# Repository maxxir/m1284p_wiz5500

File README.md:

# m1284p_wiz5500

*Read this in other languages: [English](README.md), [Русский](README.ru.md).*

Lots of projects using ATMEGA 1284p(644p partially) and Ethernet NIC Wiznet 5500.

Based on W5500 EVB examples, but heavily modified.

Building in Eclipse Kepler with AVR-Eclipse plugin and avr-gcc 4.9.2 toolchain.

## Hardware part of the projects

* [Kicad open hardware](../master/KiCad_M644_breakout_v1.2d/) 

#### This is my own m644p/m1284p custom board looks like:

#### Tested system photo:

## Software part. What done ( In order of increasing complexity and date of creation )

1. [Wiznet Loopback TCP/UDP Static IP](../master/03_m1284p_WIZNET_loopback_STATIC_IP/)
2. [Wiznet Loopback TCP/UDP DHCP IP](../master/04_m1284p_WIZNET_loopback_DHCP/)
3. [DNS example](../master/05_m1284p_WIZNET_DNS_client/)
4. [SNTP + DNS example](../master/06_m1284p_WIZNET_DNS_SNTP_client/)
5. [Telnet server example](../master/07_m1284p_WIZNET_telnets_basic/)
6. [ICMP aka ping example](../master/08_m1284p_WIZNET_ICMP_aka_ping/)
7. [Simple Web Server (one page with HTTP POST/GET queries)](../master/09_m1284p_WIZNET_simple_webserver/)
8. [HTTPD Web Server with all contents in AVR FLASH (with AJAX queries)](../master/11_m1284p_WIZNET_HTTPServer_FLASH_pages/)
9. [HTTPD Web Server with all content on SD card (Chang FAT FS lib using) (with AJAX queries)](../master/12_m1284p_WIZNET_HTTPServer_SDCARD_pages/)
10. [FTPC example (only active mode sorry) with store content on SD card (console dialog from serial terminal like putty..)](../master/14_m1284p_WIZNET_FTPC_FATFS/)
11. [FTPD example (both active-passive modes working) with store content on SD card, checked on FTP clients: Windows 7 cmd, FAR, Total commander, WinSCP.](../master/15_m1284p_WIZNET_FTPD_FATFS/)
12. [Combined HTTPD + FTPD for  dynamic upload WEB server pages, with all content on SD card (Chang FAT FS lib using) (with AJAX queries)](../master/16_m1284p_WIZNET_HTTPD_FTPD_FATFS_SDCARD/)
13. ZEVERO SD PetitFS Bootloader for both [M1284p](../master/bootloader_zevero_sd_m1284p_make/)/[M644p](../master/bootloader_zevero_sd_m644p_make/)
14. Bootloaded code: Combined Wiznet Loopback TCP/UDP Static IP + FTPD server (for bootloading via FTP client) + SD-bootloader ZEVERO, working on [M644p](../master/18_m644p_BTLD_WIZNET_LOOPBACK_FTPD_FATFS_SDCARD/)/[M1284p](../master/18_m1284p_BTLD_WIZNET_LOOPBACK_FTPD_FATFS_SDCARD/)
15. [Bootloaded code: Combined HTTPD server (with AJAX) + FTPD server (for bootloading via FTP client and upload WEB server contents) + SD-bootloader ZEVERO, working on M1284p only](../master/17_m1284p_BTLD_WIZNET_HTTPD_FTPD_FATFS_SDCARD/)
16. [IOT Blynk client Example with Blynk smartphone application (checked only Android side) - NO Arduino CODE, used Wiznet Sockets](../master/19_m1284p_WIZNET_blynk/)
17. [Bootloaded code: IOT BLYNK client combined with FTPD server (for bootloading via FTP client)+ SD-bootloader ZEVERO, working on M1284p only](../master/20_m1284p_BTLD_WIZNET_BLYNK_FTPD_FATFS_SDCARD/)
18. [TFTP client](../master/21_m1284p_WIZNET_TFTP_client_FATFS/)
19. [MQTT client](../master/22_m1284p_WIZNET_MQTT/)

#### Blynk application screenshot:

[//]: # (TODO:  Add all other links here)

## What TODO:

All done.

## Remarks:
* [m1284P schematic](../master/KiCad_M644_breakout_v1.2d/Pictures/M644_breakout_v1.2d_schematic.png/)
* [m1284P typical connection diagram](../master/KiCad_M644_breakout_v1.2d/Pictures/M644_connection_schematic.png/)
* [m1284P Board pinmap](../master/KiCad_M644_breakout_v1.2d/Pictures/M644_breakout_v1.2d_pinmap.png/)
* [Blynk IOT Application QR-code](../master/19_m1284p_WIZNET_blynk/Blynk_application/app2_m1284p_and_W5500_QR.png/)

[>>Hardware and Software parts (no Blynk) discussion your are welcome here..](https://www.avrfreaks.net/forum/need-w5500-example-c-tcp)

[>>Blynk part discussion your are welcome here..](https://community.blynk.cc/t/port-from-w5500-evb-to-atmega1284p-w5500-wiznet-sockets-library-without-arduino/35235)

## Author porting to AVR m1284p/m644p
* **Ibragimov Maksim aka maxxir**

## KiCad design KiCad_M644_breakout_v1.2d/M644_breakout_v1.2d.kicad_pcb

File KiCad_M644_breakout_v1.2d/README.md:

# AtMega 8535/16/32/324/644/1284 generic board

### Briefly about the features of the scheme:
* Nearly all GPIO pins connected to PLS terminals.
* Two GPIOs are connected: button (SW1 / PC5) and the LED (LED1 / PC4).
* External pull-up on UART RX0 / RX1.
* R-dividers for 3.3V-TTL on UART TX0 / TX1.
* SPI pins for 3 devices connected to (for example):
Ethernet (Wiz5500 / ENC28J60), Sd-Card, CAN MCP2515 and so on ...
* Compatible with **Arduino Sanguino/Mightycore**

#### Schematic:

#### This is my own custom board looks like:

#### Pinmap board (Sanguino notation):

## Author
* **Ibragimov Maksim aka maxxir**
08/04/2019

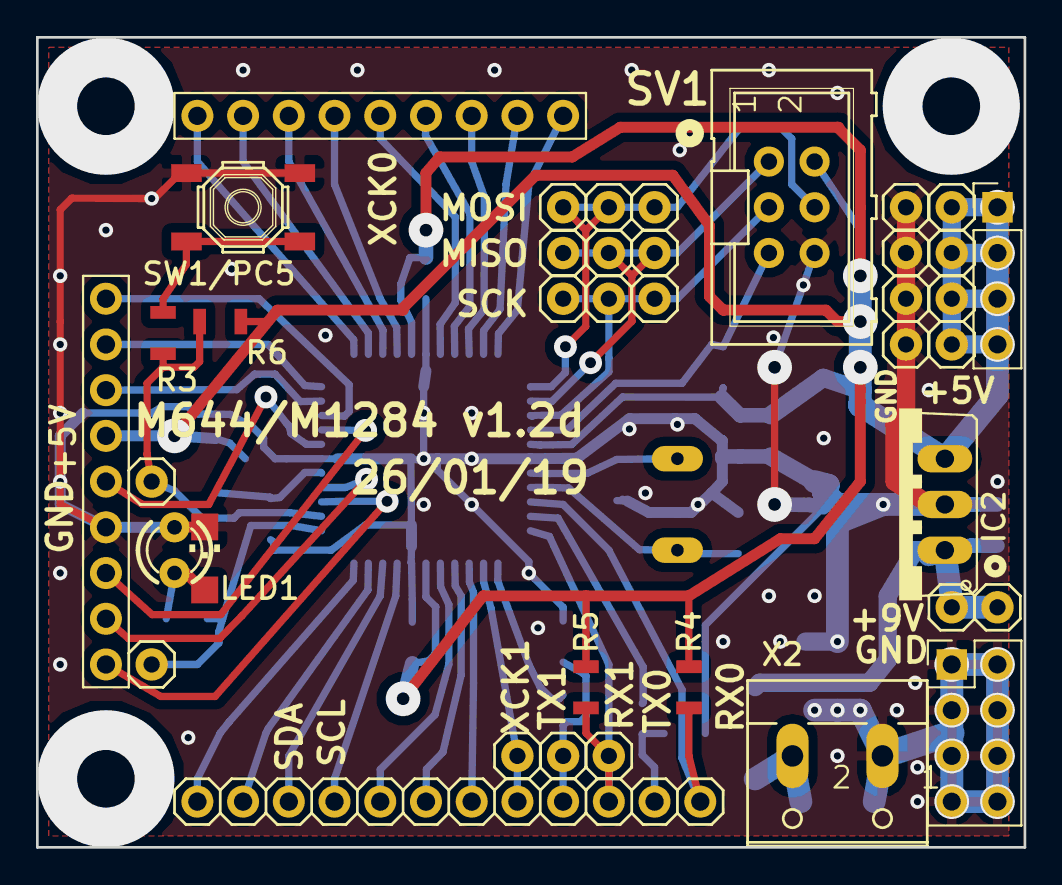
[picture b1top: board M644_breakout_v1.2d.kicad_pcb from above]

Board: 2 copper layers, 54.9 x 45.0 mm, 60 parts (0 on the bottom side), 45 nets.

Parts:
C1, C2: 18pf; C0805H
C3, C5, C7, C8, C9, C10, C11: 0.1mF; C0805H
C4: 10uF; C0805H
C6: 22uF; C0805H
C12: 100uF; D_7343-31R
D1: SM4007; DO214AA
D3: SM6T15CA; SMBJ
IC1: ATMEGA16/32/644/1284; TQFP44
IC2: 78TV; TO220V
JP1, JP2: PIN1x9; 1X09-BIG
JP3: PIN1x12; 1X12
JP4, JP5, JP6, JP7, JP8, JP9, JP10, JP11, JP12, JP13, JP14, JP15, JP16, JP17, JP19, JP20, JP21, JP22, JP24, JP25, JP26, JP27, JP28, JP29: PINx1; 1X01
L2: 10uH; L3216C
LED1: LED_RED/PC4/20; LED3MM
LED1_SMD1: LED_RED/PC4/20; CHIPLED_1206
Q1: 16Mhz; QS
R1: 1Kom; R0805H
R2: 4.7KOm; R0805H
R3: 510Om; R0805H
R4, R5: 10KOm; R0805H
R6: 10kOm; R0805H
R7, R8: 1Kom; R0805
R9, R10: 2Kom; R0805H
SV1: ISP_6PIN; ML6
SW1/PC5: SMD_TACT_4x4; SW_TACT_SMALL
X2: DG300-5.0-02P-12; W237-102

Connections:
/AREF: C3.P$2, IC1.29, JP2.5
/MISO: IC1.2, JP6.1, JP7.1, JP12.1, SV1.1
/MOSI: IC1.1, JP8.1, JP9.1, JP13.1, SV1.4
/PA0: IC1.37, JP1.6
/PA1: IC1.36, JP1.7
/PA2: IC1.35, JP1.8
/PA3: IC1.34, JP1.9
/PA4: IC1.33, JP2.2
/PA5: IC1.32, JP2.3
/PA6: IC1.31, JP2.1
/PA7: IC1.30, JP2.7
/PB0: IC1.40, JP1.5
/PB1: IC1.41, JP1.4
/PB2: IC1.42, JP1.3
/PB3: IC1.43, JP1.2
/PB4: IC1.44, JP1.1
/PC0: IC1.19, JP3.9
/PC1: IC1.20, JP3.10
/PC2: IC1.21, JP3.11
/PC3: IC1.22, JP3.12
/PC4: IC1.23, JP28.1, R1.P$1
/PC5: IC1.24, JP27.1, R3.P$2, R6.P$2
/PC6: IC1.25, JP2.9
/PC7: IC1.26, JP2.8
/PD0: IC1.9, JP3.1, R4.P$1
/PD1: IC1.10, R8.1
/PD1': JP3.2, R8.2, R10.P$1
/PD2: IC1.11, JP3.3, JP24.1, R5.P$1
/PD3: IC1.12, R7.1
/PD3': JP3.4, JP25.1, R7.2, R9.P$1
/PD4: IC1.13, JP3.5, JP26.1
/PD5: IC1.14, JP3.6
/PD6: IC1.15, JP3.7
/PD7: IC1.16, JP3.8
/RESET: IC1.4, R2.P$1, SV1.5
/SCK: IC1.3, JP4.1, JP5.1, JP11.1, SV1.3
GND: C1.P$2, C2.P$2, C3.P$1, C4.P$2, C5.P$2, C6.P$2, C7.P$2, C8.P$1, C9.P$1, C10.P$1, C11.P$2, C12.-, D3.A, IC1.6, IC1.18, IC1.28, IC1.39, IC2.2, JP2.6, JP19.1, JP20.1, JP21.1, JP22.1, LED1.K, LED1_SMD1.C, R9.P$2, R10.P$2, SV1.6, SW1/PC5.3, SW1/PC5.4, X2.1
unnamed: C1.P$1, IC1.7, Q1.2
unnamed: C2.P$1, IC1.8, Q1.1
unnamed: C4.P$1, C5.P$1, D1.C, IC2.1, JP10.1, JP29.1
unnamed: C11.P$1, IC1.27, L2.2
unnamed: D1.A, D3.C, X2.2
unnamed: LED1.A, LED1_SMD1.A, R1.P$2
unnamed: R3.P$1, SW1/PC5.1, SW1/PC5.2
VCC: C6.P$1, C7.P$1, C8.P$2, C9.P$2, C10.P$2, C12.+, IC1.5, IC1.17, IC1.38, IC2.3, JP2.4, JP14.1, JP15.1, JP16.1, JP17.1, L2.1, R2.P$2, R4.P$2, R5.P$2, R6.P$1, SV1.2

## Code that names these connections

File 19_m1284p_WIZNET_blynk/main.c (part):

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 * OK (v1.8) Need compare local blynk.c code with modern <blynk> library - (Too old version here - 0.2.1 (On git blynk March 2019 - 0.6.x) )
 * OK (v1.8) Made fix correction blynk.h/blynk.c 16.02.2019 to match BLYNK protocol 0.6.0
 * OK (v1.9) Two feedback examples from:
 * 			 D20/PC4(digitalWrite(20))->V20(virtualRead(20))
 * 			 PWM D15/PD7(analogWrite(15))->V15(virtualRead(15))
 * 			 using push events && on change state flags
 * PS.
 * Further correction, or advices about the code from BLYNK authors (Vladimir Shimansky, Dmitriy Dumanskiy ..) is highly desirable.
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
//*********************************Timer2 PWM: BEGIN
/*
 * Handle PWM out PD7-PIN15:
 * OCR2A = 0/127/255; Duty 0/50/100%

 * Handle PWM out PD6-PIN14:
 * OCR2B = 0/127/255; Duty 0/50/100%

 */
void pwm8bit_timer2_init(void)
{
	//PWM on TIMER2 (PD7/OC2A) &&  TIMER2 (PD6/OC2B)
	// PHASE CORRECT PWM 8-bit mode setup
	// 31.25kHz FREQ OUT / 0.98kHz FREQ OUT

	// Set PD7 to OUT
	DDRD |= (1<<7);
	// Set PD6 to OUT
	DDRD |= (1<<6);
	/*
	 * Clear OCnA/OCnB/OCnC on compare
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			if(v15_changed)
			{
				v15_changed = 0; //Drop flag
				//Push message with changed V15 value (LED PWM PIN15/PD7 )
				blynk_push_virtual_pin(15);

			}
			else if(v20_changed)
			{
				v20_changed = 0; //Drop flag
				//Push message with changed V20 value (LED1 D20/PC4)
				blynk_push_virtual_pin(20);
			}
			//Every 10sec event for LED2 PIN13, and uptime device
			if(++timer_led2_push_10sec == 10)
			{
				timer_led2_push_10sec = 0; //Clear timer_led2..
				//Every 10sec toggle, and push LED2 PIN13/PD5 state to BLYNK server (widget Value Display)
				led2_tgl();
				blynk_push_pin(13);

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
	sw1_conf();//SW1 internal pull-up

	pwm8bit_timer2_init(); // PD7/OC2A used as PHASE CORRECT 8bit PWM (0.98kHz FREQ OUT)

	sei(); //re-enable global interrupts

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
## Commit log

2019-01-18 First commit for 00_m1284p_blink project
2019-01-18 First commit for 00_m1284p_blink_make
2019-01-18 Fixed text encode to UTF8, added .gitignore
2019-01-18 Delete de.innot.avreclipse.core.prefs
    Clean prj
2019-01-18 Update README.md
    Update readme
2019-01-18 Added 01_m1284p_bb00_minimum project
2019-01-18 Create global .gitignore rule
2019-01-18 Gitignore correction
2019-01-18 Add 02_m1284p_FATFS_Chang_tst project
2019-01-18 Add 02_m1284p_FATFS_LFN_Chang_tst project
2019-01-18 Add 03_m1284p_WIZNET_loopback_STATIC_IP project
2019-01-18 Add 03_m1284p_WIZNET_loopback_FATFS_template project
2019-01-18 Minor changes at <b>03_m1284p_WIZNET_loopback_FATFS_template</b>
2019-01-18 Add [04_m1284p_WIZNET_loopback_DHCP] prj
2019-01-18 Add [05_m1284p_WIZNET_DNS_client] prj
2019-01-18 Add [06_m1284p_WIZNET_DNS_SNTP_client] prj
2019-01-18 Add [07_m1284p_WIZNET_telnets_basic] prj
2019-01-18 Add [08_m1284p_WIZNET_ICMP_aka_ping] prj
2019-01-18 Add [09_m1284p_WIZNET_simple_webserver] prj
2019-01-18 Add [10_m1284p_WIZNET_HTTPServer_RAM_pages] prj
2019-01-18 Add [11_m1284p_WIZNET_HTTPServer_FLASH_pages] prj
2019-01-18 Add [11_m644p_WIZNET_HTTPServer_FLASH_pages] prj
2019-01-18 Add [12_m1284p_WIZNET_HTTPServer_SDCARD_pages] prj
2019-01-18 Minor changes [12_m1284p_WIZNET_HTTPServer_SDCARD_pages]
2019-01-18 Change text encode to UTF-8
2019-01-18 Change text encode to UTF8
2019-01-18 Add [14_m1284p_WIZNET_FTPC_FATFS_v1.2] prj
2019-01-18 Add [15_m1284p_WIZNET_FTPD_FATFS] project
2019-01-18 Add [16_m1284p_WIZNET_HTTPD_FTPD_FATFS_SDCARD] prj
2019-01-18 Add [17_m1284p_BTLD_WIZNET_HTTPD_FTPD_FATFS_SDCARD] prj
2019-01-18 Add [bootloader_zevero_sd_m1284p_make] bootloader prj
2019-01-18 Add Makefile to local .gitignore
2019-01-18 Add to [00_m1284p_blink_make] .gitignore
2019-01-18 Add double-IP config for [03_m1284p_WIZNET_loopback_FATFS_template]
2019-01-18 Add double-IP config for [03_m1284p_WIZNET_loopback_STATIC_IP]
2019-01-18 Add double-IP config for [05_m1284p_WIZNET_DNS_client]
2019-01-18 Add double-IP config for [04_m1284p_WIZNET_loopback_DHCP]
2019-01-18 Add double-IP config for [06_m1284p_WIZNET_DNS_SNTP_client]
2019-01-18 Add double-IP config for [07_m1284p_WIZNET_telnets_basic]
2019-01-20 Add double-IP config for [08_m1284p_WIZNET_ICMP_aka_ping]
2019-01-20 Some minor changes and add double-IP config for [09_m1284p_WIZNET_simple_webserver]
2019-01-20 Some minor changes and add double-IP config for [10_m1284p_WIZNET_HTTPServer_RAM_pages]
2019-01-20 Some minor changes and add double-IP config for [11_m1284p_WIZNET_HTTPServer_FLASH_pages]
2019-01-20 Some minor changes and add double-IP config for [11_m644p_WIZNET_HTTPServer_FLASH_pages]
2019-01-21 Rename project 14_m1284p_WIZNET_FTPC_FATFS_v1.2 to 14_m1284p_WIZNET_FTPC_FATFS
2019-01-21 Add double-IP config for [12_m1284p_WIZNET_HTTPServer_SDCARD_pages]
2019-01-21 Fix some minor typos
2019-01-22 Add double-IP config for [14_m1284p_WIZNET_FTPC_FATFS]
2019-01-25 Add double-IP config for [15_m1284p_WIZNET_FTPD_FATFS]
2019-01-28 Add double-IP config for [16_m1284p_WIZNET_HTTPD_FTPD_FATFS_SDCARD]
2019-02-04 Change target hex name for [bootloader_zevero_sd_m1284p_make]
2019-02-04 Add double-IP config for [17_m1284p_BTLD_WIZNET_HTTPD_FTPD_FATFS_SDCARD]
2019-02-06 Add new test project [00_m644p_blink_make]
2019-02-06 Add new project [12_m644p_WIZNET_HTTPServer_SDCARD_pages]
2019-02-07 Fixed typo in [12_m644p_WIZNET_HTTPServer_SDCARD_pages]
2019-02-07 Renamed bootable image to 1284BOOT.BIN [bootloader_zevero_sd_m1284p_make]
2019-02-07 Rename bootable image to 1284BOOT.BIN, add globals.c [17_m1284p_BTLD_WIZNET_HTTPD_FTPD_FATFS_SDCARD]
2019-02-12 Add project [bootloader_zevero_sd_m644p_make]
2019-02-12 Builded BIN changed to 1284BOOT.BIN in [00_m1284p_blink_make]
2019-02-12 Builded BIN changed to 644BOOT.BIN at [00_m644p_blink_make]
2019-02-13 Add new project [18_m1284p_BTLD_WIZNET_LOOPBACK_FTPD_FATFS_SDCARD]
2019-02-13 Add new project [18_m644p_BTLD_WIZNET_LOOPBACK_FTPD_FATFS_SDCARD]
2019-02-15 Add FTPD authorization abilities to [17_m1284p_BTLD_WIZNET_HTTPD_FTPD_FATFS_SDCARD]
2019-02-15 Add FTPD authorization abilities to [18_m1284p_BTLD_WIZNET_LOOPBACK_FTPD_FATFS_SDCARD]
2019-02-15 Add FTPD authentication abilities to [18_m644p_BTLD_WIZNET_LOOPBACK_FTPD_FATFS_SDCARD]
2019-03-12 Add globals.c in [03_m1284p_WIZNET_loopback_STATIC_IP]
2019-03-12 Add new project for IOT testing [19_m1284p_WIZNET_blynk]
2019-03-12 Added DNS resolver to [19_m1284p_WIZNET_blynk], slightly optimized code. Tested on M644p - OK.
2019-03-12 Fixed and tested digitalRead with Value Display application widget
2019-03-12 Corrected typo
2019-03-14 Add and test analog Read-Write [19_m1284p_WIZNET_blynk]
2019-03-14 Added blynk_syncAll to [19_m1284p_WIZNET_blynk]
2019-03-14 Fixed typo
2019-03-15 Add push event (P13/PD.5 toggle every 10 sec && send state P13 to BLYNK server)
2019-03-15 (v1.7) Add push event to Virtual PIN1. Every 10sec push message: "Uptime: xxx sec", to BLYNK server (widget Terminal)
2019-03-15 Fixed typos
2019-03-15 Fixed push send buffer blynk_push_virtual_pin_msg(..)
2019-03-15 Clean comments
2019-03-15 Another clean comments :))
2019-03-16 Made fix correction blynk.h/blynk.c 16.02.2019 to match BLYNK protocol 0.6.0
2019-03-16 Add KiCad Hardware design M1284p board with factory gerbers [KiCad_M644_breakout_v1.2d]
2019-03-16 Remove my private token from project
2019-03-16 Add demo application QR-code
2019-03-16 Add pics: photo and screenshot
2019-03-16 Edit comments
2019-03-16 add README.md
2019-03-16 Fixed README.md
2019-03-16 Another README.md fix
2019-03-16 README.md corrected
2019-03-16 Comments and README.md corrected.
2019-03-17 Slightly edited the pics and scheme
2019-03-17 Slightly edited the pics and pcb hardware board
2019-03-18 Added in extern auth[]
2019-03-18 Added git commands tips
2019-03-18 Added Two feedback examples
2019-03-18 Add new application screenshot
2019-03-18 Added Prologue for fast WDT disable
2019-03-18 Another edited README.md
2019-03-19 Added Android Blynk app v2 QR-code
2019-03-23 Added 1284BOOT.BIN.bootloaded (ie. precompiled binary example).
2019-03-23 Added 644BOOT.BIN.bootloaded (ie. precompiled binary example).
2019-03-23 Added readme about using precompiled binaries.
2019-03-23 Added project [20_m1284p_BTLD_WIZNET_BLYNK_FTPD_FATFS_SDCARD]
2019-03-23 Added Blynk application helper files
2019-03-23 Added blynk application related files
2019-03-23 Added DNS related files.
2019-03-23 Fixed globals.h/globals.c
2019-03-23 Update globals.c
    Fixed auth[] token
2019-03-23 All OK
2019-03-24 Added *.hex.example to [12_m1284p_WIZNET_HTTPServer_SDCARD_pages]
2019-03-24 Added in globals.h selector SPI Speed 4/8Mhz
2019-03-25 Added selector SPI Speed 4/8Mhz
2019-03-25 Cleaned SPI code driver
2019-03-25 Updated SPI code driver
2019-03-25 Updated SPI code driver.
2019-03-25 Updated 1284BOOT.BIN example
2019-03-25 Updated 644BOOT.BIN example
2019-03-25 Removed deprecated files
2019-03-25 Removed reprecated files
2019-03-25 Added TFP-client project (not working yet)
2019-03-25 TFTP code writing begin..
2019-03-26 First positive steps in TFTP client working..
2019-03-27 TFTP test updated
2019-03-27 Tested transfer large files ~220kbytes is OK
2019-03-27 Write-in data to SD-card file "readme_txt" and another patterns during TFTP transfer session - SUCCESS.
2019-03-28 Added patterns to check TFTP received data. All woks good now.
2019-03-29 Added handlers for CHK_RAM_LEAKAGE && CHK_UPTIME
2019-03-30 Reduced PWM frequency till ~ 1 kHz
2019-03-31 All my debug code in tftp.c replace PRINTF(..) to DBG_PRINT(INFO_DBG, ..)
2019-03-31 Added FSM for TFTP client in main loop, and WIZNET standard TCP/UDP loopback
2019-03-31 Removed temporary debug.log.
2019-04-04 Added new factory design 1.2d-a
2019-04-05 Added globals.h/globals.c and made some minor modifications.
2019-04-05 Made some minor changes
2019-04-05 Added some minor changes.
2019-04-05 Added MQTT Client example (template)
2019-04-06 MQTT client testing is OK
2019-04-06 Added analize MQTT publish result (for MQTT failover mode)
2019-04-07 Cleared from garbage
2019-04-07 Added .gitignore for KiCad
2019-04-07 Updated PCB design
2019-04-07 Added new pics
2019-04-07 Added two every seconds topics, briefly section, optimized code.
2019-04-07 Added two 1-sec topics, briefly section, optimized code.
2019-04-07 Added some minor comments.
2019-04-08 Added tiny pics for EasyElectronics article
2019-04-09 Changed pics
2019-04-09 Remove 3 diodes
2019-04-09 Added readme.md to PCB design
2019-04-13 Slightly corrected schematic layout
2019-04-24 Updated m1284_w5500 photo
